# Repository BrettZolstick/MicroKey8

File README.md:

# MicroKey8
An 8 key rhythm game controller that uses microswitches commonly found in mice for short travel and advanced debounce logic.

<div align="center">

</div>

## Project Overview
## Build Instructions
## Firmware

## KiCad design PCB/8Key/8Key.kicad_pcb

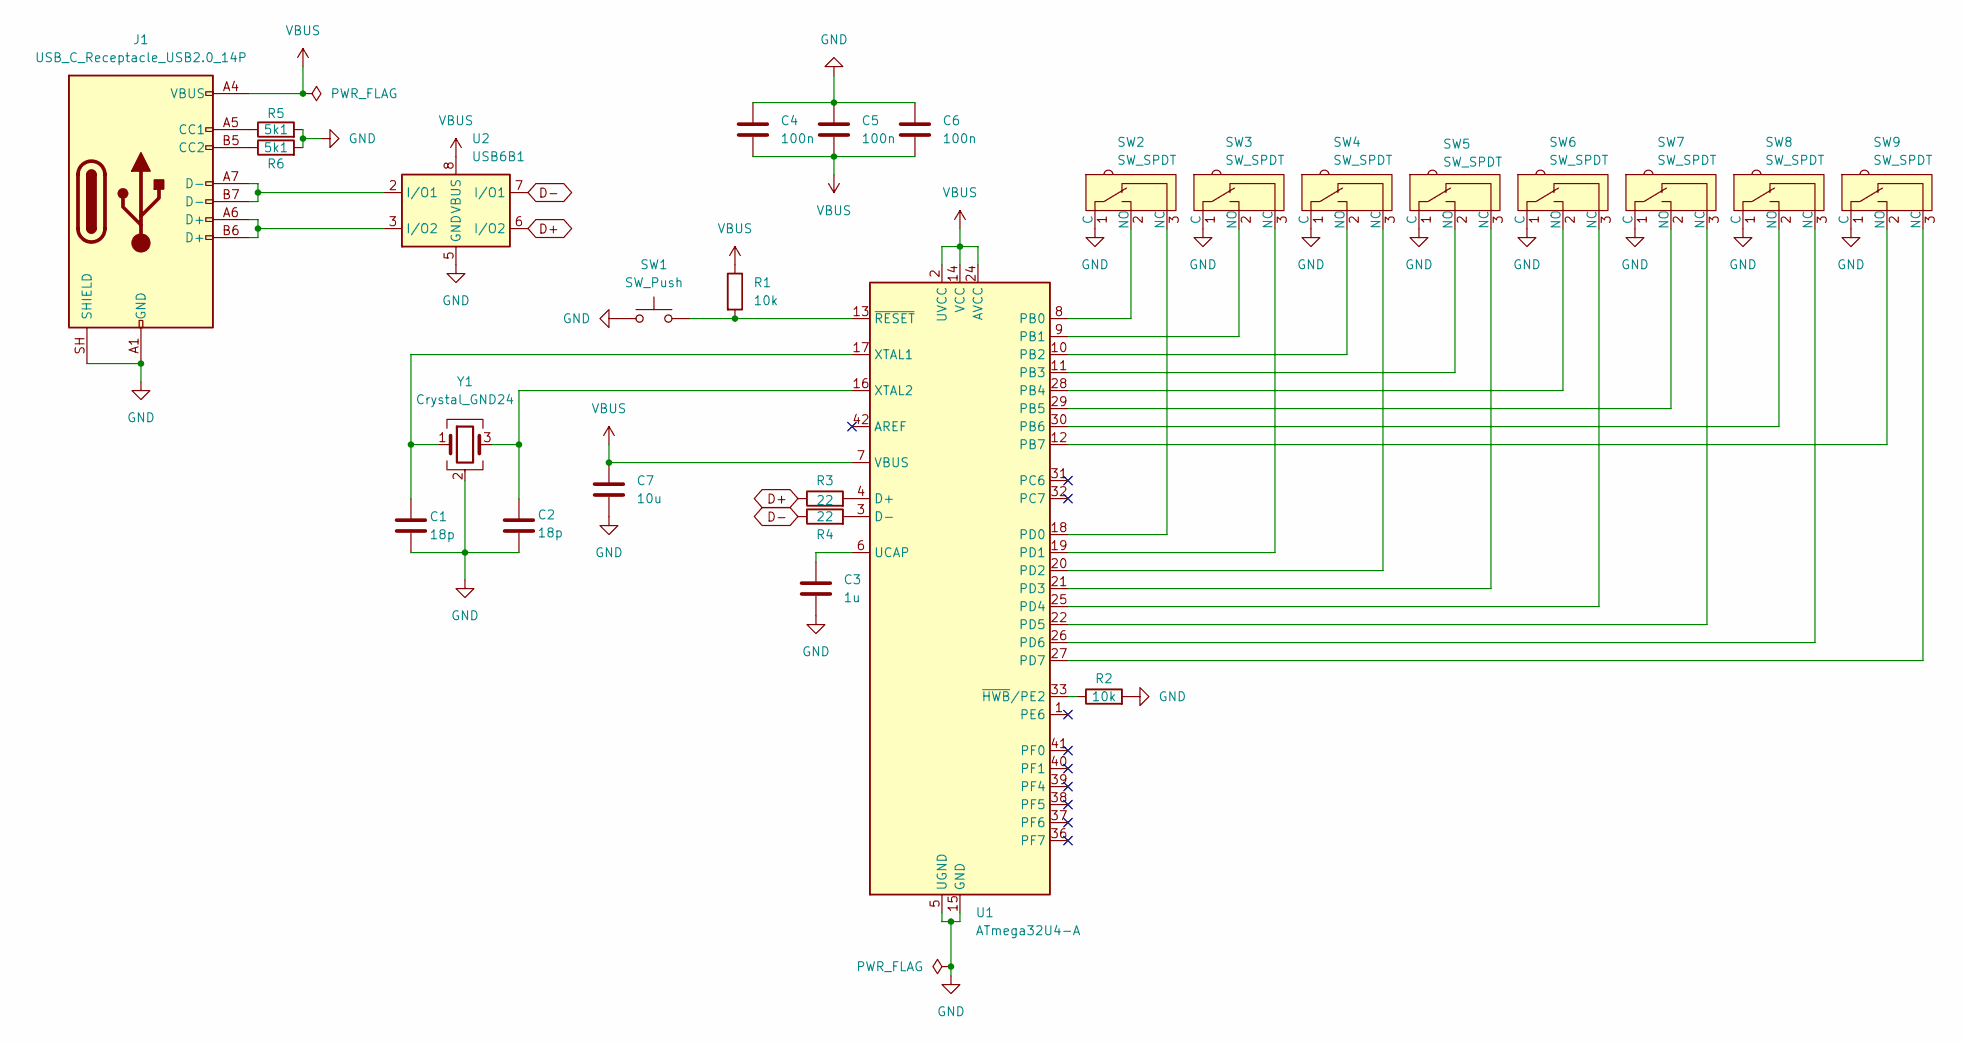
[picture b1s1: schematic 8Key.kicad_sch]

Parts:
C1, C2: 18p; C_0805_2012Metric; LCSC Part # C1797
C3: 1u; C_0805_2012Metric; LCSC Part # C28323
C4, C5, C6: 100n; C_0805_2012Metric; LCSC Part # C49678
C7: 10u; C_1206_3216Metric; LCSC Part # C13585
J1: USB_C_Receptacle_USB2.0_14P; USB_C_Receptacle_GCT_USB4110; LCSC Part # C5143397
R1, R2: 10k; R_0805_2012Metric; LCSC Part # C2907219
R3, R4: 22; R_0805_2012Metric; LCSC Part # C2907310
R5, R6: 5k1; R_0805_2012Metric; LCSC Part # C2073749
SW1: SW_Push; SW_Push_SPST_NO_Alps_SKRK; LCSC Part # C115357
SW2, SW3, SW4, SW5, SW6, SW7, SW8, SW9: SW_SPDT; SW_Micro_Switch; LCSC Part # C397278
U1: ATmega32U4-A; TQFP-44_10x10mm_P0.8mm; LCSC Part # C2052746
U2: USB6B1; SOIC-8_3.9x4.9mm_P1.27mm; LCSC Part # C10508
Y1: Crystal_GND24; Crystal_SMD_Abracon_ABM8G-4Pin_3.2x2.5mm; LCSC Part # C112972

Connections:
D+: R3.1, U2.6 (I/O2)
D-: R4.1, U2.7 (I/O1)
GND: C1.2, C2.2, C3.2, C4.1, C5.1, C6.1, C7.2, J1.A1 (GND), J1.A12 (GND), J1.B1 (GND), J1.B12 (GND), J1.SH (SHIELD), R2.2, R5.2, R6.2, SW1.1, SW2.1 (C), SW3.1 (C), SW4.1 (C), SW5.1 (C), SW6.1 (C), SW7.1 (C), SW8.1 (C), SW9.1 (C), U1.5 (UGND), U1.15 (GND), U1.23 (GND), U1.35 (GND), U1.43 (GND), U2.4 (GND), U2.5 (GND), Y1.2 (G), Y1.4 (G)
unnamed: J1.A5 (CC1), R5.1
unnamed: J1.B5 (CC2), R6.1
unnamed: J1.A6 (D+), J1.B6 (D+), U2.3 (I/O2)
unnamed: J1.A7 (D-), J1.B7 (D-), U2.2 (I/O1)
unnamed: SW2.3 (NC), U1.18 (PD0)
unnamed: SW2.2 (NO), U1.8 (PB0)
unnamed: SW3.3 (NC), U1.19 (PD1)
unnamed: SW3.2 (NO), U1.9 (PB1)
unnamed: SW4.3 (NC), U1.20 (PD2)
unnamed: SW4.2 (NO), U1.10 (PB2)
unnamed: SW5.3 (NC), U1.21 (PD3)
unnamed: SW5.2 (NO), U1.11 (PB3)
unnamed: SW6.3 (NC), U1.25 (PD4)
unnamed: SW6.2 (NO), U1.28 (PB4)
unnamed: SW7.3 (NC), U1.22 (PD5)
unnamed: SW7.2 (NO), U1.29 (PB5)
unnamed: SW8.3 (NC), U1.26 (PD6)
unnamed: SW8.2 (NO), U1.30 (PB6)
unnamed: SW9.3 (NC), U1.27 (PD7)
unnamed: SW9.2 (NO), U1.12 (PB7)
unnamed: R3.2, U1.4 (D+)
unnamed: R4.2, U1.3 (D-)
unnamed: C3.1, U1.6 (UCAP)
unnamed: C1.1, U1.17 (XTAL1), Y1.1
unnamed: C2.1, U1.16 (XTAL2), Y1.3
unnamed: R2.1, U1.33 (~HWB/PE2)
unnamed: R1.2, SW1.2, U1.13 (~RESET)
VBUS: C4.2, C5.2, C6.2, C7.1, J1.A4 (VBUS), J1.A9 (VBUS), J1.B4 (VBUS), J1.B9 (VBUS), R1.1, U1.2 (UVCC), U1.7 (VBUS), U1.14 (VCC), U1.24 (AVCC), U1.34 (VCC), U1.44 (AVCC), U2.1 (VBUS), U2.8 (VBUS)

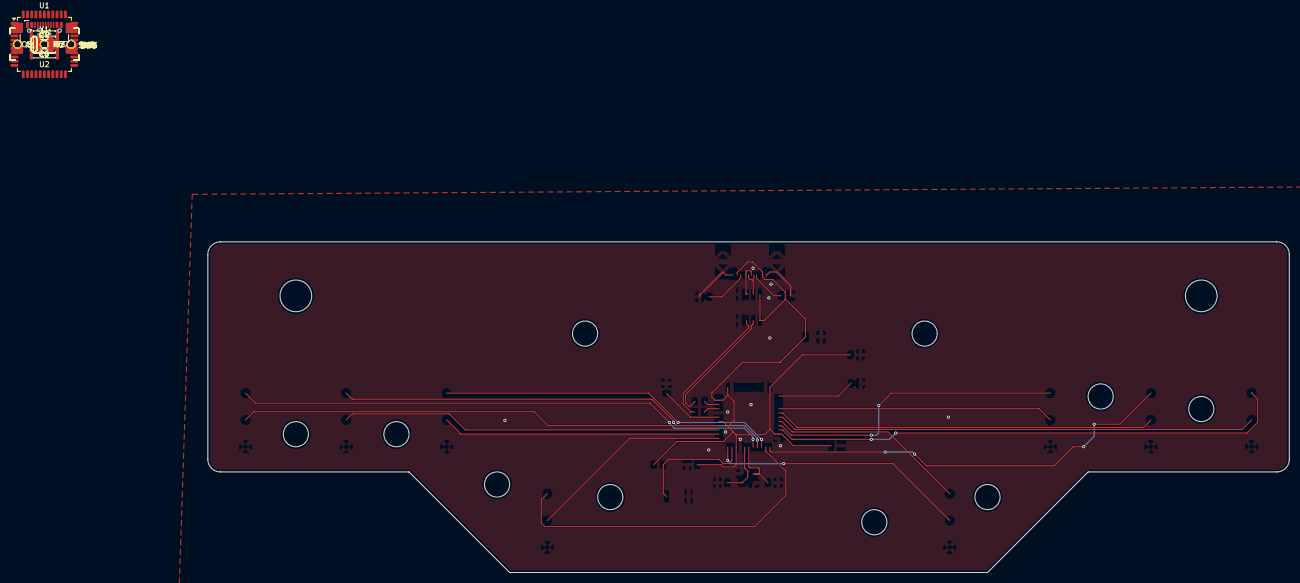
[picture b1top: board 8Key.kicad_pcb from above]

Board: 2 copper layers, 204.8 x 62.6 mm, 26 parts (0 on the bottom side), 31 nets.
